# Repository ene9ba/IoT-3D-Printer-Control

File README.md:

# IoT-3D-Printer-Control
Control Unit with ESP 8266 to control enclosure LED, cabon filter and analyse Temperature, Fan-Spee, Flamesensor, Smokesensor

CAD files you can find at [grabcad](https://grabcad.com/library/3d-printer-enclosure-7) or [thingeverse](https://www.thingiverse.com/thing:6453549)

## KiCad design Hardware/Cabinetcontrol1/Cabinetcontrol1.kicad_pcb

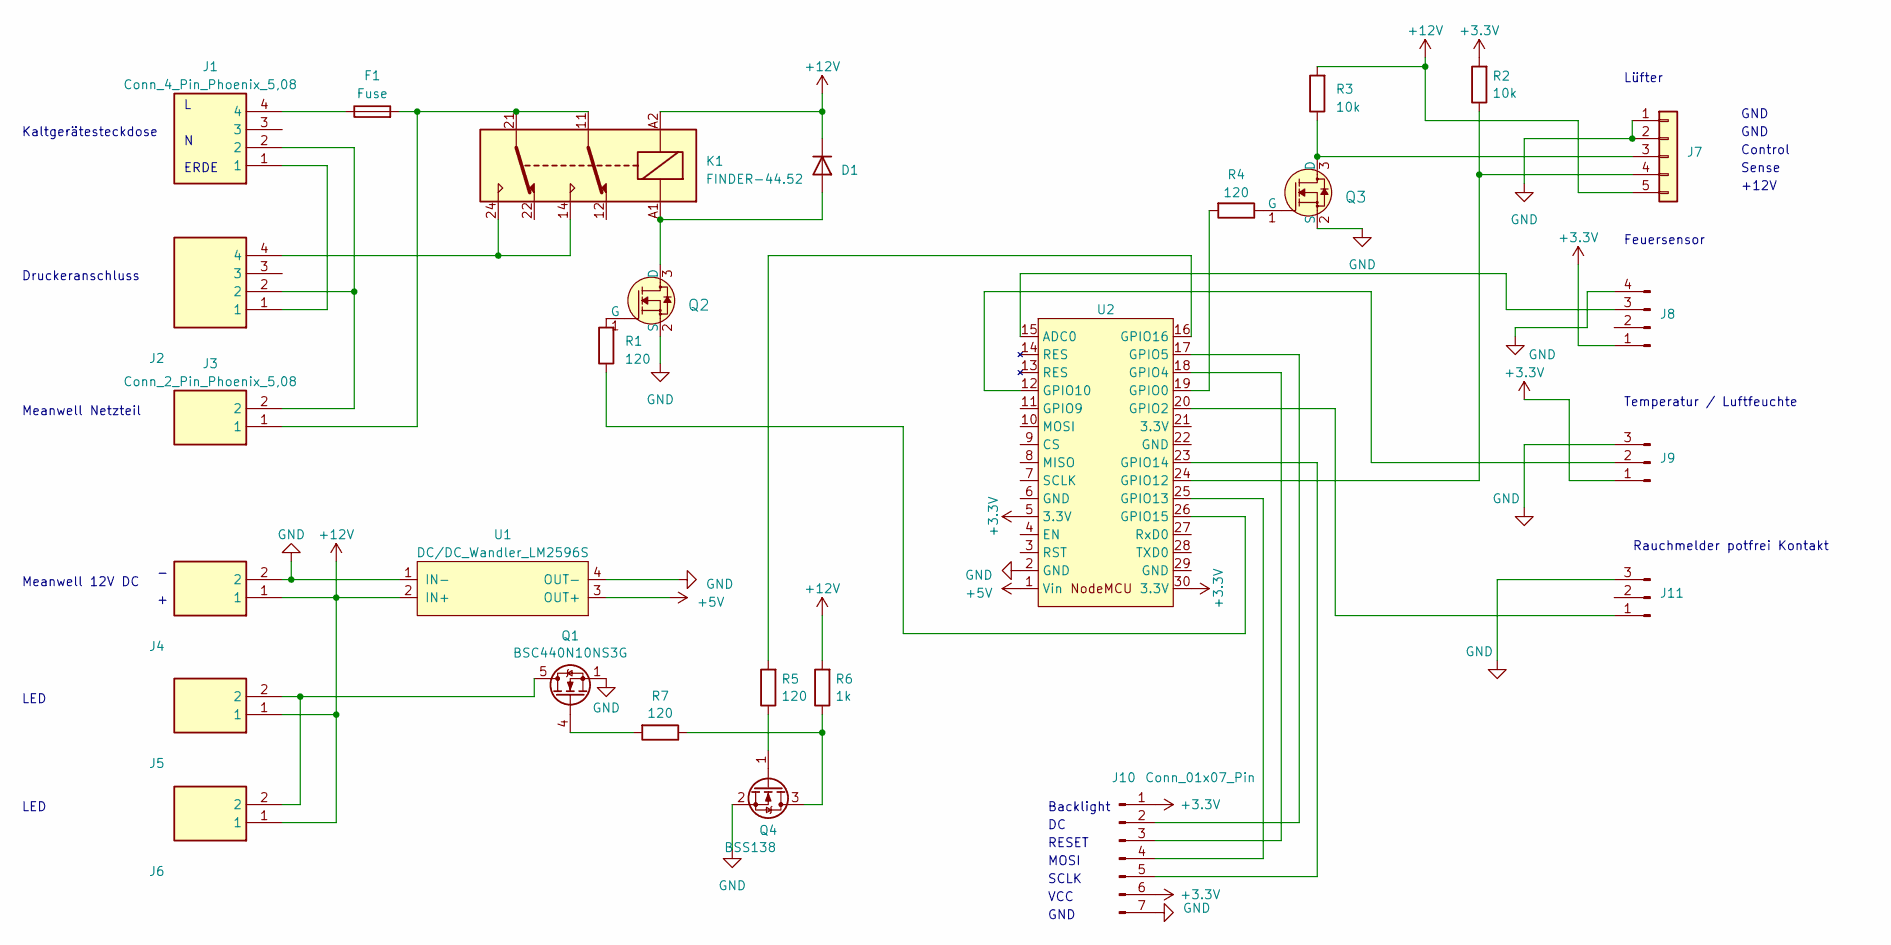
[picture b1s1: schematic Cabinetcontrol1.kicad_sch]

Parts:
D1: MBRS 1100 SMD Schottkydiode, 100 V, 1 A, DO-214AA; D_SMB_Handsoldering
F1: Fuse; Sicherungssockel rund
J1, J2: Conn_4_Pin_Phoenix_5,08; 1757268; Manufacturer_Part_Number 1757268; Mouser Part Number 651-1757268
J3, J4, J5, J6: Conn_2_Pin_Phoenix_5,08; 1757242; Manufacturer_Part_Number 1757242; Mouser Part Number 651-1757242
J7: Conn_01x05; JST_XH_B5B-XH-AM_1x05_P2.50mm_Vertical
J8: Conn_01x04_Pin_JST-XHP; JST_XH_B4B-XH-A_1x04_P2.50mm_Vertical
J9, J11: Conn_01x03_Pin; JST_XH_B3B-XH-A_1x03_P2.50mm_Vertical
J10: Conn_01x07_Pin; JST_XH_B7B-XH-A_1x07_P2.50mm_Vertical
K1: FINDER-44.52; Relay_DPDT_Finder_40.52
Q1: BSC440N10NS3G; TDSON-8-1
Q2, Q3: IRLML2402TRPBF; SOT95P237X112-3N; MPN IRLML2402TRPBF; Digi-Key_PN IRLML2402PBFCT-ND
Q4: BSS138; SOT-23
R1, R4, R5, R7: 120; R_0805_2012Metric_Pad1.20x1.40mm_HandSolder
R2, R3: 10k; R_0805_2012Metric_Pad1.20x1.40mm_HandSolder
R6: 1k; R_0805_2012Metric_Pad1.20x1.40mm_HandSolder
U1: DC/DC_Wandler_LM2596S; LM2596S_MODULE
U2: NodeMCU

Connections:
+3.3V: J8.1, J9.1, J10.1, J10.6, R2.2, U2.5 (3.3V), U2.30 (3.3V)
+5V: U1.3 (OUT+), U2.1 (Vin)
+12V: D1.1 (K), J4.1, J5.1, J6.1, J7.5, K1.A2, R3.2, R6.2, U1.2 (IN+)
GND: J4.2, J7.1, J7.2, J8.4, J9.3, J10.7, J11.3, Q1.1 (S), Q1.2 (S), Q1.3 (S), Q2.2 (S), Q3.2 (S), Q4.2 (S), U1.1 (IN-), U1.4 (OUT-), U2.2 (GND)
unnamed: D1.2 (A), K1.A1, Q2.3 (D)
unnamed: F1.1, J1.4
unnamed: F1.2, J3.1, K1.11, K1.21
unnamed: J1.1, J2.1
unnamed: J1.2, J2.2, J3.2
unnamed: J2.4, K1.14, K1.24
unnamed: J7.3, Q3.3 (D), R3.1
unnamed: J7.4, R2.1, U2.24 (GPIO12)
unnamed: J8.3, U2.15 (ADC0)
unnamed: J9.2, U2.12 (GPIO10)
unnamed: J10.2, U2.17 (GPIO5)
unnamed: J10.3, U2.18 (GPIO4)
unnamed: J10.4, U2.25 (GPIO13)
unnamed: J10.5, U2.23 (GPIO14)
unnamed: J11.1, U2.20 (GPIO2)
unnamed: J5.2, J6.2, Q1.5 (D)
unnamed: Q1.4 (G), R7.2
unnamed: Q2.1 (G), R1.2
unnamed: Q3.1 (G), R4.1
unnamed: Q4.3 (D), R6.1, R7.1
unnamed: Q4.1 (G), R5.1
unnamed: R4.2, U2.19 (GPIO0)
unnamed: R1.1, U2.26 (GPIO15)
unnamed: R5.2, U2.16 (GPIO16)

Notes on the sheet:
VCC
ERDE
Meanwell Netzteil
RESET
Lüfter
GND
Kaltgerätesteckdose
Backlight
Control
Druckeranschluss
Feuersensor
Meanwell 12V DC
+12V
LED
Temperatur / Luftfeuchte
Rauchmelder potfrei Kontakt
Sense
SCLK
MOSI

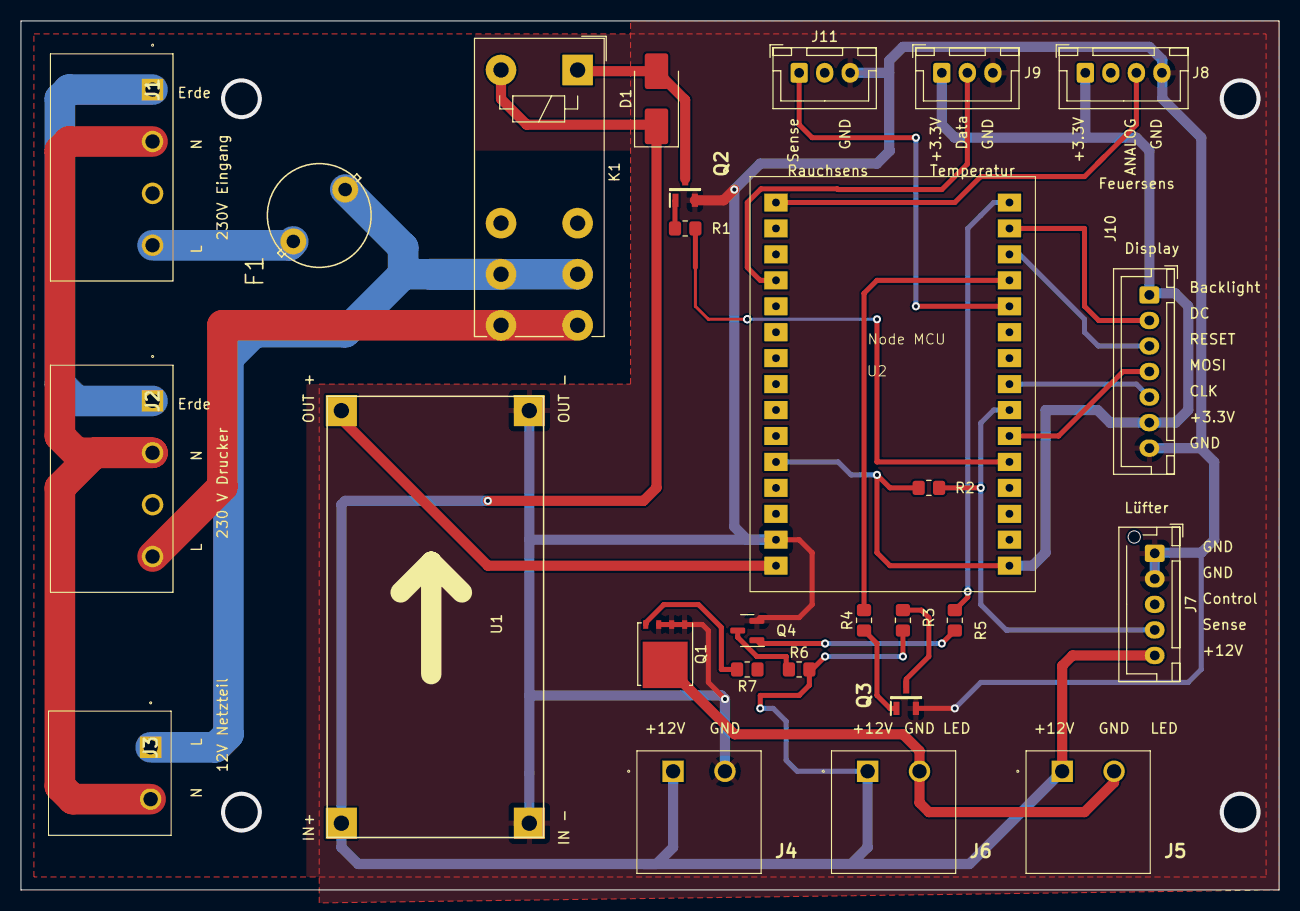
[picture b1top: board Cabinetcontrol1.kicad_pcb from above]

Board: 2 copper layers, 123.2 x 85.1 mm, 27 parts (0 on the bottom side), 28 nets.

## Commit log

2024-01-27 readme
2024-03-16 Version 1.10 v. 16.03.2024 ntp hinzugefügt las message Meldung geht an mqtt
2024-03-17 test
2024-09-24 Version 1.20 v. 24.09.2024 mqtt mit user und passort, reconnect getestet
2026-02-08 Version 1.21 v. 08.02.2026 mqtt domain name changed from docker-home to docker-home.castle
2026-06-18 mqtt address changed
